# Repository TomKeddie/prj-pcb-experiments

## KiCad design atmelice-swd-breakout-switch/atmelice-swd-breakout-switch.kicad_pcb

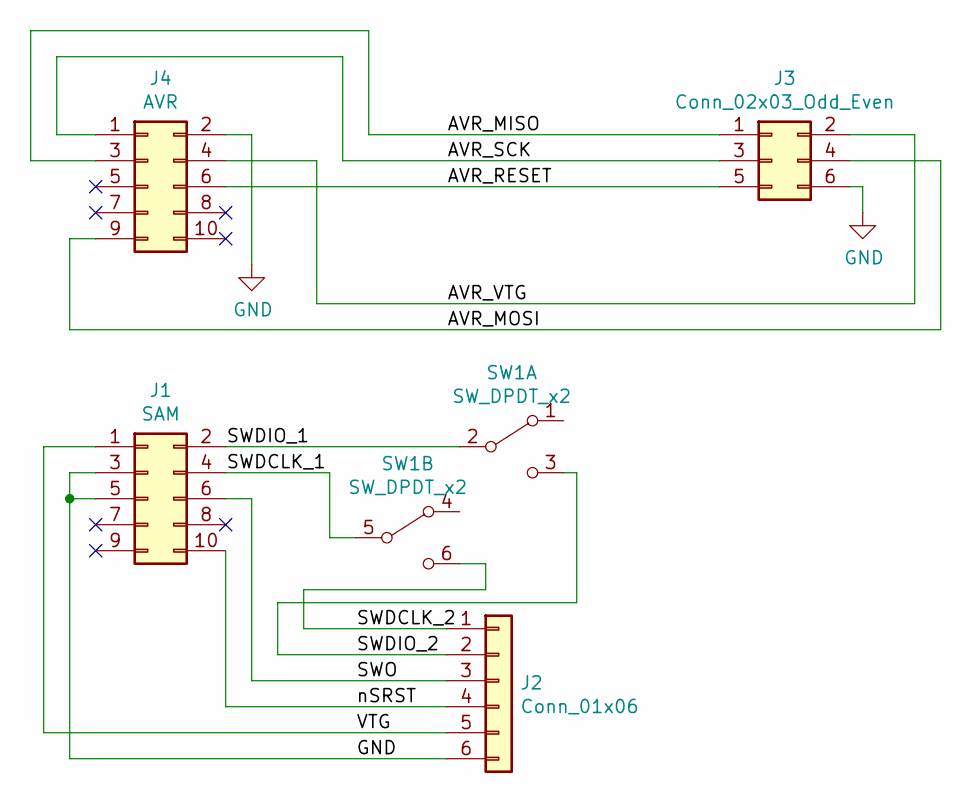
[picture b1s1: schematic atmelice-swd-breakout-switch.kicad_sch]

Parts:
J1: SAM; PinSocket_2x05_P1.27mm_Vertical
J2: Conn_01x06; PinHeader_1x06_P2.54mm_Vertical
J3: Conn_02x03_Odd_Even; PinHeader_2x03_P2.54mm_Vertical
J4: AVR; PinSocket_2x05_P1.27mm_Vertical
SW1: SW_DPDT_x2; SW_DPDT_SMD

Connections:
/AVR_MISO: J3.1, J4.3
/AVR_MOSI: J3.4, J4.9
/AVR_RESET: J3.5, J4.6
/AVR_SCK: J3.3, J4.1
/AVR_VTG: J3.2, J4.4
/SWDCLK_1: J1.4, SW1.5 (B)
/SWDCLK_2: J2.1, SW1.6 (C)
/SWDIO_1: J1.2, SW1.2 (B)
/SWDIO_2: J2.2, SW1.3 (C)
/SWO: J1.6, J2.3
/VTG: J1.1, J2.5
/nSRST: J1.10, J2.4
GND: J1.3, J1.5, J2.6, J3.6, J4.2

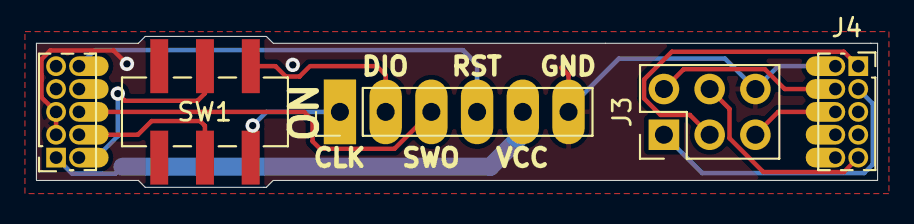
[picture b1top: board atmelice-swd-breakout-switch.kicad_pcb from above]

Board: 2 copper layers, 46.7 x 8.4 mm, 5 parts (0 on the bottom side), 13 nets.
